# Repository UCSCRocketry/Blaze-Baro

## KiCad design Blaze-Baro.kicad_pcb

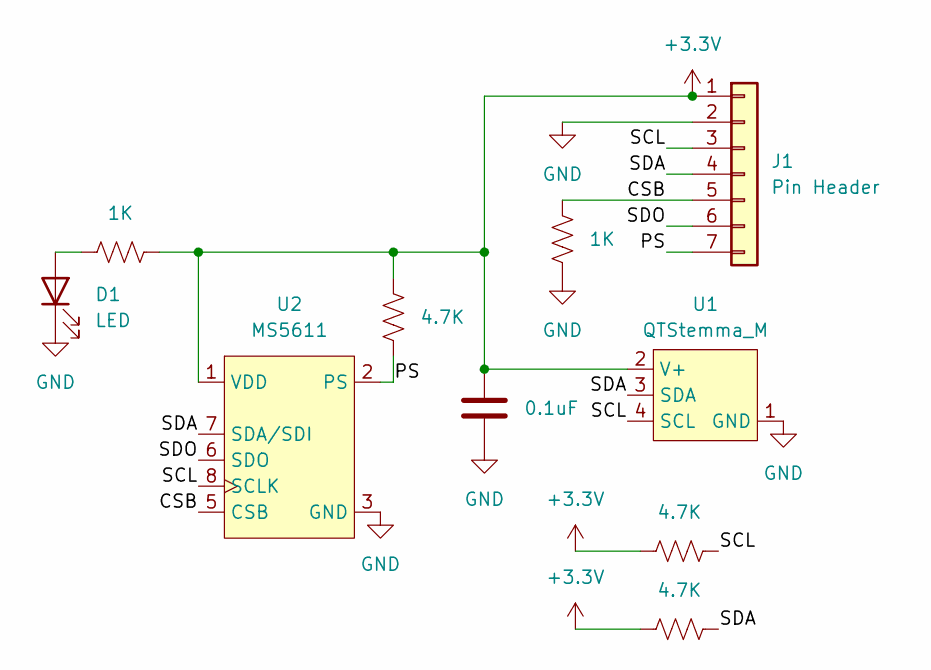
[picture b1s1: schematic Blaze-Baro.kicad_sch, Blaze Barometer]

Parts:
C1: 0.1uF; C_0603_1608Metric
D1: LED; LED_0603_1608Metric
J1: Pin Header; MS5611
R1, R2: 1K; R_0603_1608Metric
R3, R4, R5: 4.7K; R_0603_1608Metric
U1: QTStemma_M; JST_SH_SM04B-SRSS-TB_1x04-1MP_P1.00mm_Horizontal
U2: MS5611; XDCR_MS561101BA03-50

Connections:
+3.3V: C1.2, J1.1, R1.1, R3.2, R4.2, R5.1, U1.2 (V+), U2.1 (VDD)
/CSB: J1.5, R2.1, U2.4 (CSB), U2.5 (CSB)
/PS: J1.7, R5.2, U2.2 (PS)
/SCL: J1.3, R3.1, U1.4 (SCL), U2.8 (SCLK)
/SDA: J1.4, R4.1, U1.3 (SDA), U2.7 (SDA/SDI)
/SDO: J1.6, U2.6 (SDO)
GND: C1.1, D1.1 (K), J1.2, R2.2, U1.1 (GND), U2.3 (GND)
unnamed: D1.2 (A), R1.2

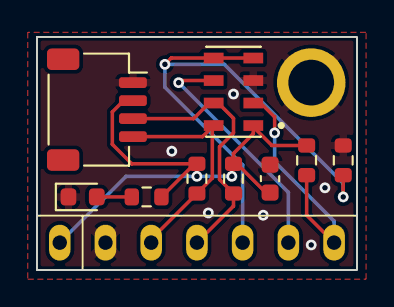
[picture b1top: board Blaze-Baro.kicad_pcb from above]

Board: 2 copper layers, 17.8 x 13.0 mm, 10 parts (0 on the bottom side), 8 nets.

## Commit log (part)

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2026-02-07 Project setup
2026-02-16 Started blaze barometer
2026-03-03 all past changes to blaze baro
2026-03-06 push recent changes added stemma qt footprint
2026-03-12 Redid schematic
2026-03-13 Started work on pcb connections
2026-03-17 Closer to final PCB design
2026-03-18 Finished design :)
2026-03-18 Power net update
2026-03-18 Added i2c addr to silk
